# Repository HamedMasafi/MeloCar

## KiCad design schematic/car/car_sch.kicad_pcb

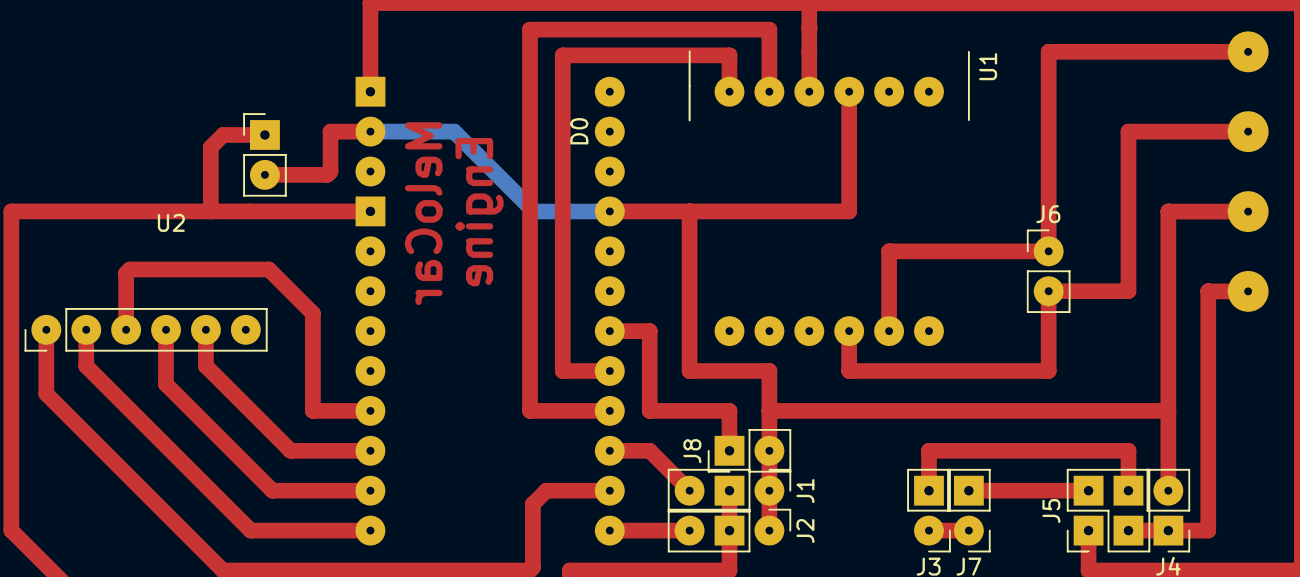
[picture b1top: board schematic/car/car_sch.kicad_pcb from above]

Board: 2 copper layers, 11 parts (1 on the bottom side), 17 nets.

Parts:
A3: Arduino_Pro_Mini_Socket_NoSPH
J1: Led; PinHeader_1x03_P2.54mm_Vertical
J2: Servo; PinHeader_1x03_P2.54mm_Vertical
J3: Battery; PinHeader_1x02_P2.54mm_Vertical
J4: Power; PinHeader_1x02_P2.54mm_Vertical
J5: Switch; PinHeader_2x02_P2.54mm_Vertical
J6: MOTOR-CTRL; PinHeader_1x02_P2.54mm_Vertical
J7: BarGraph; PinHeader_1x02_P2.54mm_Vertical
J8: Horn; PinHeader_1x02_P2.54mm_Vertical
U1: DRV8833PW; TSSOP-16_4.4x5mm_P0.65mm
U2: NRF24L01_Breakout; NRF24L01

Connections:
+5V: A3.Vcc1 (Vcc), J1.2, J2.2, U2.2 (VCC)
+8V: A3.RAW, J4.1, J5.1, J5.3, U1.11 (VCP)
+BATT: J3.2, J5.2, J5.4, J7.2
-BATT: J3.1, J7.1
GND: A3.GND1 (GND), A3.GND2 (GND), J1.1, J2.1, J4.2, J8.2, U1.13 (GND), U2.1 (GND)
NRF_CE: A3.D8, U2.3 (CE)
NRF_CSN: A3.D10 (D10_CS), U2.4 (~CSN)
NRF_MISO: A3.D12 (D12_MISO), U2.7 (MISO)
NRF_MOSI: A3.D11 (D11_MOSI), U2.6 (MOSI)
NRF_SCK: A3.D13 (D13_SCK), U2.5 (SCK)
unnamed: J6.1, U1.2 (AOUT1)
unnamed: J6.2, U1.4 (AOUT2)
PIN_HORN: A3.D4, J8.1
PIN_LED: A3.D7, J1.3
PIN_MOTOR_1: A3.D5, U1.16 (AIN1)
PIN_MOTOR_2: A3.D6, U1.15 (AIN2)
PIN_SERVO: A3.D9, J2.3

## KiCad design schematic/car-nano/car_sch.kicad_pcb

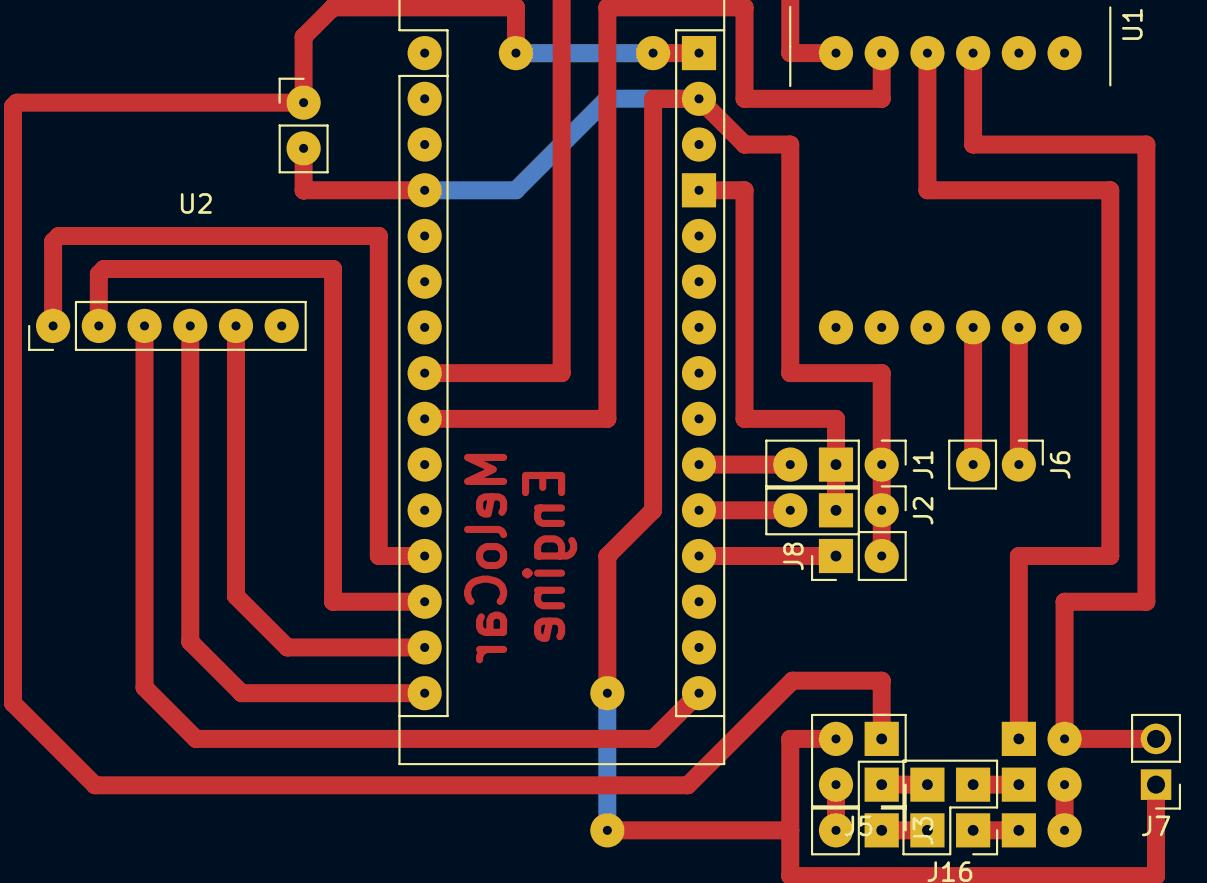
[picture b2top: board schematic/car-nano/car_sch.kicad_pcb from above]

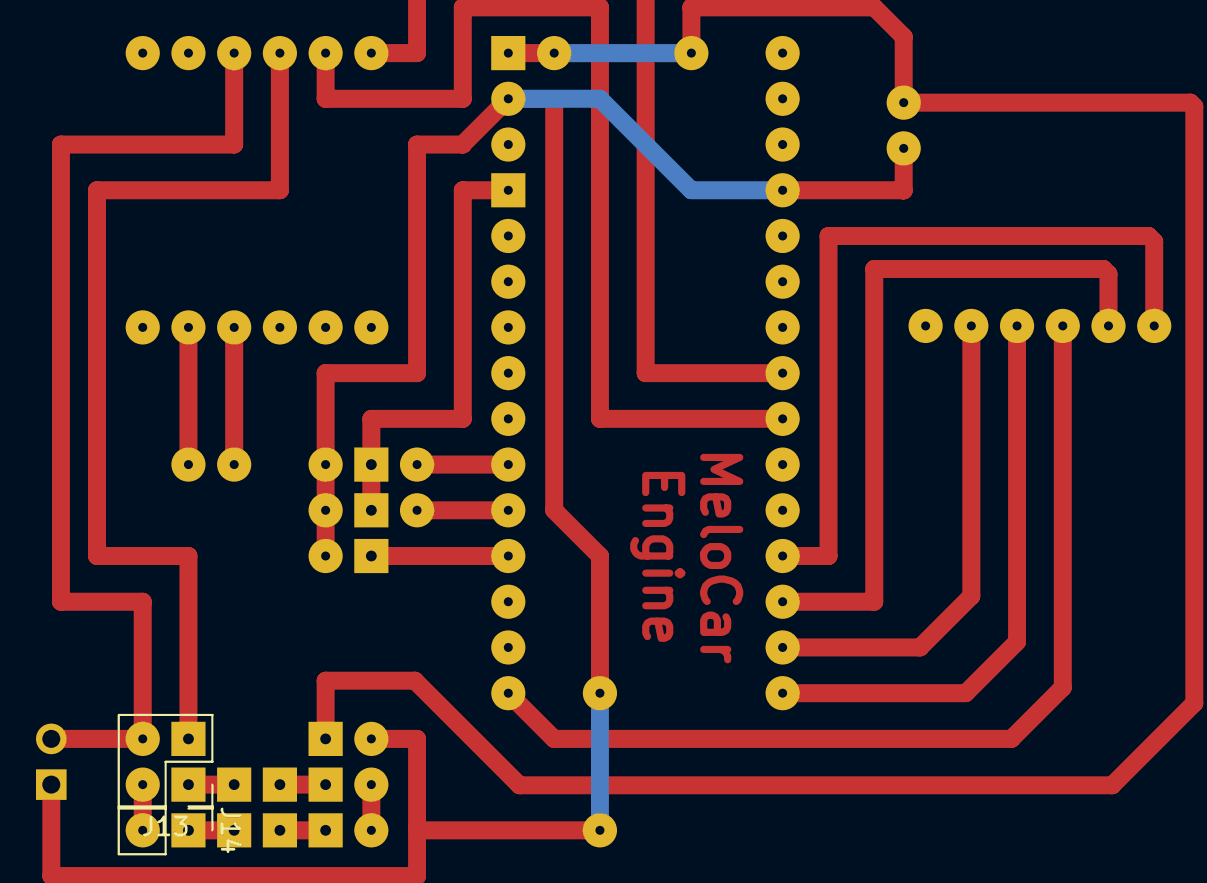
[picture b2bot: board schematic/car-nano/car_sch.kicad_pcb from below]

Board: 2 copper layers, 13 parts (2 on the bottom side), 22 nets.

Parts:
A2: Arduino_Nano_Every; Arduino_Nano
J1: Led; PinHeader_1x03_P2.54mm_Vertical
J2: Servo; PinHeader_1x03_P2.54mm_Vertical
J3: Input-Micro; PinHeader_1x02_P2.54mm_Vertical
J5: Regulator-5v; PinHeader_2x02_P2.54mm_Vertical
J6: MOTOR-CTRL; PinHeader_1x02_P2.54mm_Vertical
J7: Motor_Power; PinHeader_1x02_P2.54mm_Vertical
J8: Horn; PinHeader_1x02_P2.54mm_Vertical
J13: Regulator-9v; PinHeader_2x02_P2.54mm_Vertical
J14: Input-Motor; PinHeader_1x02_P2.54mm_Vertical
J16: Button; PinHeader_2x02_P2.54mm_Vertical
U1: DRV8833PW; TSSOP-16_4.4x5mm_P0.65mm
U2: NRF24L01_Breakout; NRF24L01

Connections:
+5V: A2.30 (VIN), J1.2, J2.2, J5.3, U2.2 (VCC)
+9V: J13.3, U1.11 (VCP)
GND1: J7.2, J13.4, U1.13 (GND)
GND2: A2.4 (GND), A2.29 (GND), J1.1, J2.1, J5.4, J7.1, J8.2, U2.1 (GND)
NRF_CE: A2.12 (D9), U2.3 (CE)
NRF_CSN: A2.13 (D10), U2.4 (~CSN)
NRF_MISO: A2.14 (MOSI), U2.7 (MISO)
NRF_MOSI: A2.15 (MISO), U2.6 (MOSI)
NRF_SCK: A2.16 (SCK), U2.5 (SCK)
unnamed: J3.2, J5.2
unnamed: J6.1, U1.2 (AOUT1)
unnamed: J6.2, U1.4 (AOUT2)
unnamed: J13.1, J16.3
unnamed: J13.2, J14.2
unnamed: J14.1, J16.1
unnamed: J3.1, J16.2
unnamed: J5.1, J16.4
PIN_HORN: A2.19 (A0), J8.1
PIN_LED: A2.21 (A2), J1.3
PIN_MOTOR_1: A2.8 (D5), U1.16 (AIN1)
PIN_MOTOR_2: A2.9 (D6), U1.15 (AIN2)
PIN_SERVO: A2.20 (A1), J2.3

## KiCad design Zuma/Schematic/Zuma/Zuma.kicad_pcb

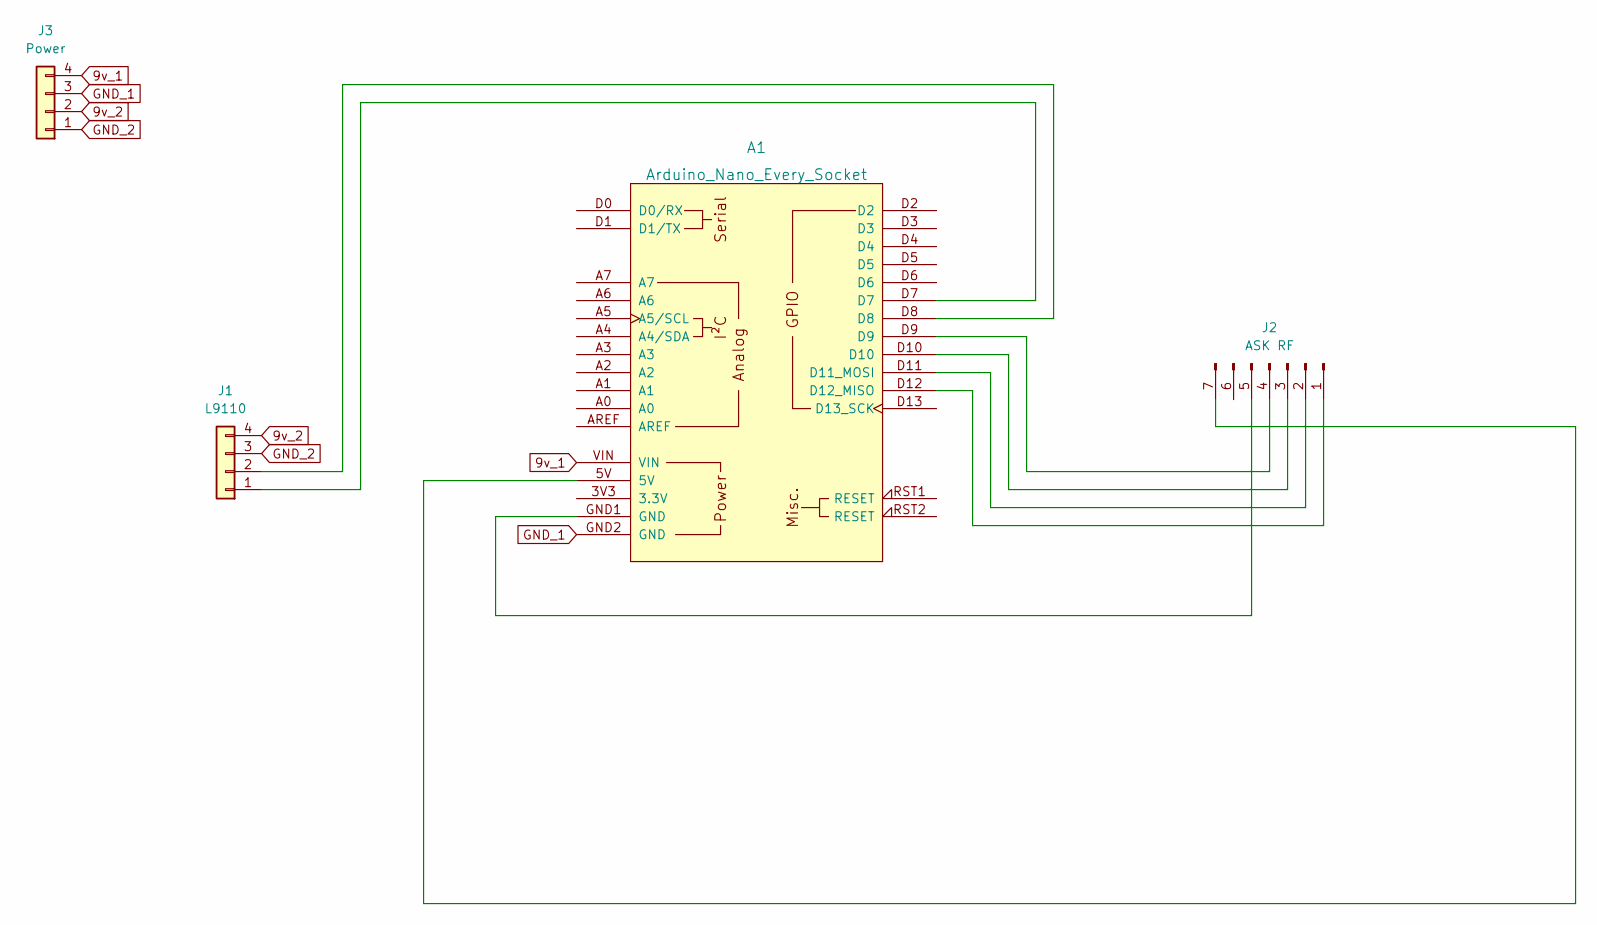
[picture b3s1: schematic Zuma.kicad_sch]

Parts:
A1: Arduino_Nano_Every_Socket
J1: L9110; PinHeader_1x04_P2.54mm_Vertical
J2: ASK RF; PinHeader_1x07_P2.54mm_Vertical
J3: Power; PinHeader_1x04_P2.54mm_Vertical

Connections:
9v_1: A1.VIN, J3.4
9v_2: J1.4, J3.2
GND_1: A1.GND2 (GND), J3.3
GND_2: J1.3, J3.1
unnamed: A1.D7, J1.1
unnamed: A1.D8, J1.2
unnamed: A1.D10, J2.3
unnamed: A1.D11 (D11_MOSI), J2.2
unnamed: A1.D12 (D12_MISO), J2.1
unnamed: A1.GND1 (GND), J2.5
unnamed: A1.D9, J2.4
unnamed: A1.5V, J2.7

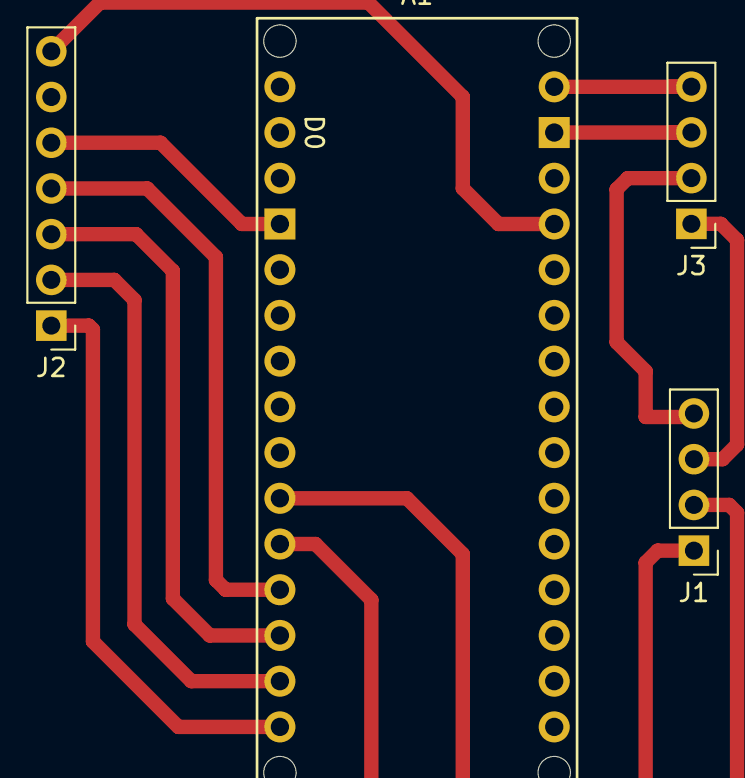
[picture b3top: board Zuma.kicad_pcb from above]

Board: 2 copper layers, 4 parts (0 on the bottom side), 12 nets.

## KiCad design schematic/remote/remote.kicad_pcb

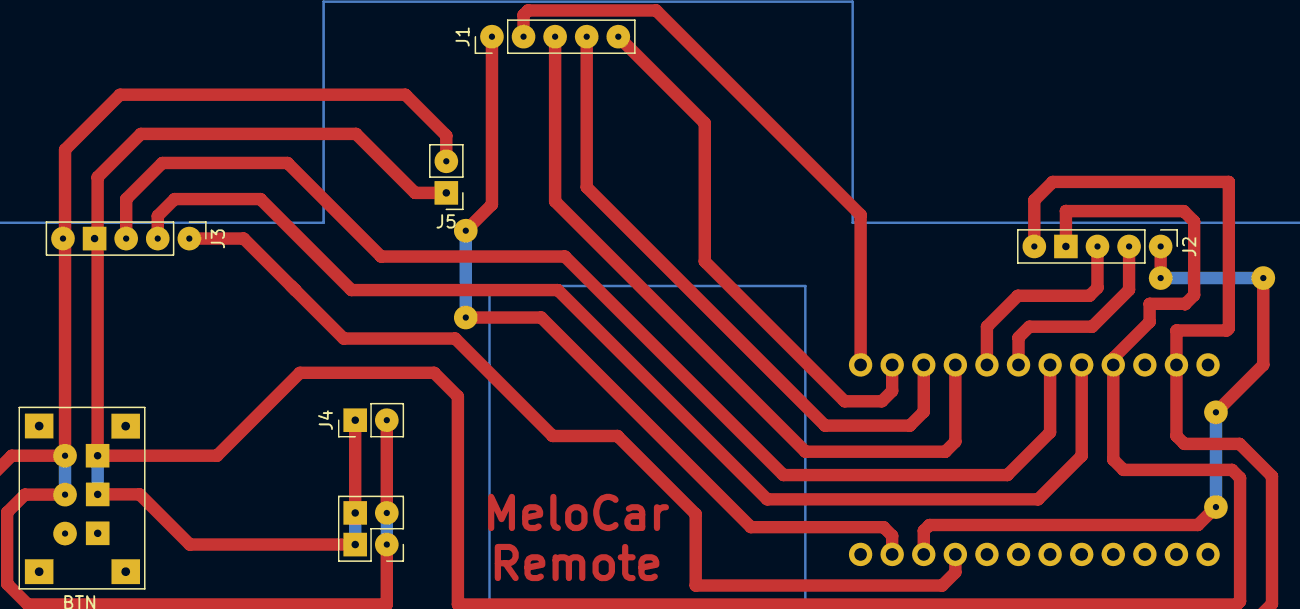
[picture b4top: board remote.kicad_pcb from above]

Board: 2 copper layers, 7 parts (1 on the bottom side), 13 nets.

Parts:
BTN: PushButton_6_pin
J1: Conn_01x05_Male; PinHeader_1x05_P2.54mm_Vertical
J2: Joystick_Left; PinHeader_1x05_P2.54mm_Vertical
J3: Joystick_Right; PinHeader_1x05_P2.54mm_Vertical
J4: Micro-Power-IN; PinHeader_1x02_P2.54mm_Vertical
J5: NRF-Power; PinHeader_1x02_P2.54mm_Vertical
U1: ARDUINO_PRO_MINI; MODULE_ARDUINO_PRO_MINI

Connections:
+5V: BTN.3, BTN.5, J2.4, J3.4, J4.1, J5.1, U1.JP6_4 (VCC_1)
GND: BTN.4, BTN.6, J2.5, J3.5, J4.2, J5.2, U1.JP6_2 (GND_1)
unnamed: J1.1, U1.JP7_2 (D8)
unnamed: J1.2, U1.JP6_12 (D10)
unnamed: J1.3, U1.JP6_9 (SCK)
unnamed: J1.4, U1.JP6_10 (MISO)
unnamed: J1.5, U1.JP6_11 (MOSI)
unnamed: J2.1, U1.JP7_3 (D7)
unnamed: J2.3, U1.JP6_8 (A0)
unnamed: J3.1, U1.JP7_4 (D6)
unnamed: J3.2, U1.JP6_5 (A3)
unnamed: J3.3, U1.JP6_6 (A2)
unnamed: J2.2, U1.JP6_7 (A1)

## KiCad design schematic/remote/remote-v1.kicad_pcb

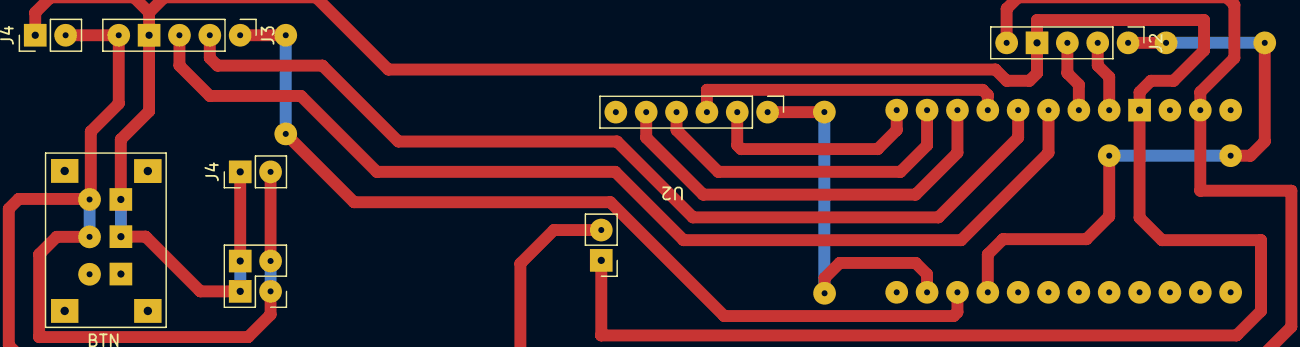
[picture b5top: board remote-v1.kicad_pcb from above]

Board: 2 copper layers, 7 parts (1 on the bottom side), 13 nets.

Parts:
BTN: PushButton; PushButton_6_pin
J2: Joystick_Right; PinHeader_1x05_P2.54mm_Vertical
J3: Joystick_Left; PinHeader_1x05_P2.54mm_Vertical
J4, J4#2: Power-IN; PinHeader_1x02_P2.54mm_Vertical
U1: ARDUINO_PRO_MINI; MODULE_ARDUINO_PRO_MINI
U2: NRF24L01

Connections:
+5V: BTN.3, BTN.5, J2.4, J3.4, J4.1, J4#2.1, U1.JP6_4 (VCC_1), U2.2 (VCC)
GND: BTN.4, BTN.6, J2.5, J3.5, J4.2, J4#2.2, U1.JP6_2 (GND_1), U2.1 (GND)
unnamed: J2.1, U1.JP7_4 (D6)
unnamed: J2.2, U1.JP6_5 (A3)
unnamed: J2.3, U1.JP6_6 (A2)
unnamed: J3.1, U1.JP7_3 (D7)
unnamed: J3.2, U1.JP6_8 (A0)
unnamed: J3.3, U1.JP6_7 (A1)
unnamed: U1.JP6_9 (SCK), U2.5 (SCK)
unnamed: U1.JP6_10 (MISO), U2.7 (MISO)
unnamed: U1.JP6_11 (MOSI), U2.6 (MOSI)
unnamed: U1.JP6_12 (D10), U2.4 (~CSN)
unnamed: U1.JP7_2 (D8), U2.3 (CE)

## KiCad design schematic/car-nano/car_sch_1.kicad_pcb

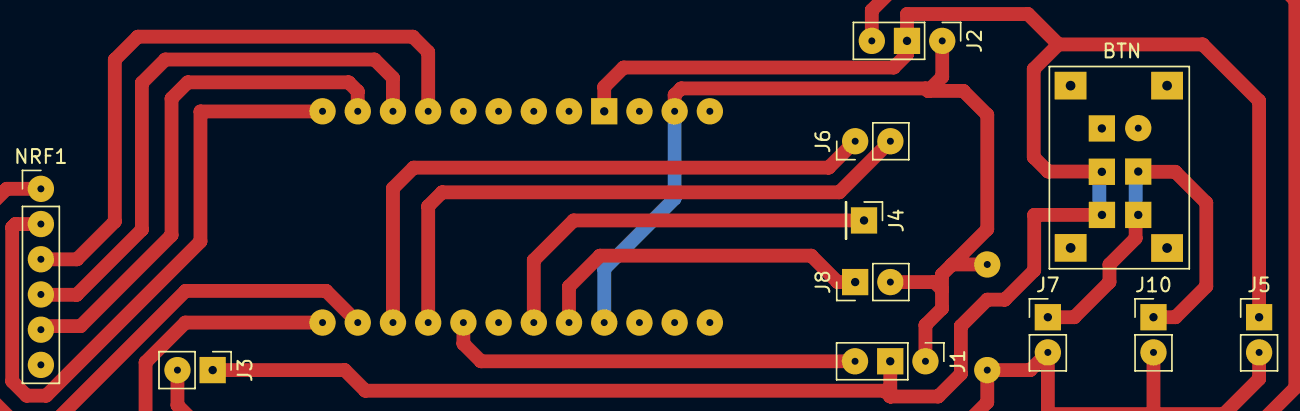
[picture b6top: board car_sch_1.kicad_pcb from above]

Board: 2 copper layers, 12 parts (1 on the bottom side), 14 nets.

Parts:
BTN: PushButton_6_pin
J1: Led; PinHeader_1x03_P2.54mm_Vertical
J2: Servo; PinHeader_1x03_P2.54mm_Vertical
J3: NRF-Power; PinHeader_1x02_P2.54mm_Vertical
J4: Accel; PinHeader_1x01_P2.54mm_Vertical
J5: Micro-Power-IN; PinHeader_1x02_P2.54mm_Vertical
J6: MOTOR-CTRL; PinHeader_1x02_P2.54mm_Vertical
J7: MOTOR-PWR-OUT; PinHeader_1x02_P2.54mm_Vertical
J8: Horn; PinHeader_1x02_P2.54mm_Vertical
J10: Motor-PWR-IN; PinHeader_1x02_P2.54mm_Vertical
NRF1: Conn_01x06_Male; PinHeader_1x06_P2.54mm_Vertical
U1: ARDUINO_PRO_MINI; MODULE_ARDUINO_PRO_MINI

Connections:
+5V: BTN.3, BTN.5, J1.2, J2.2, J3.1, J5.1, U1.JP6_4 (VCC_1)
+12V: BTN.4, BTN.6, J7.1, J10.1
GND: J1.1, J2.1, J3.2, J5.2, J7.2, J8.2, J10.2, U1.JP6_2 (GND_1), U1.JP7_9 (GND_2)
unnamed: J1.3, U1.JP7_5 (D5)
unnamed: J2.3, U1.JP7_1 (D9)
unnamed: J6.1, U1.JP7_3 (D7)
unnamed: J6.2, U1.JP7_4 (D6)
unnamed: J8.1, U1.JP7_8 (D2)
unnamed: NRF1.3, U1.JP6_9 (SCK)
unnamed: NRF1.4, U1.JP6_10 (MISO)
unnamed: NRF1.5, U1.JP6_11 (MOSI)
unnamed: NRF1.2, U1.JP6_12 (D10)
unnamed: NRF1.1, U1.JP7_2 (D8)
unnamed: J4.1, U1.JP7_7 (D3)

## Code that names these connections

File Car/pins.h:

#pragma once

// #define PIN_ACCEL   3
#define PIN_BEEP    4
#define PIN_MOTOR_1 5
#define PIN_MOTOR_2 6
#define LED_PIN     7
#define PIN_SERVO   9

#define PIN_CE      8
#define PIN_CSN     10

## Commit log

2022-10-31 Initial
2022-11-02 wip: nrf
2022-11-05 OOps; ws works
2022-11-07 platformio
2022-11-07 Back to arduino ide
2022-11-07 /stepper/blinker/
2022-11-09 Servo port changed to 5
2022-11-09 Remote
2022-11-17 --wip-- [skip ci]
2022-11-17 wip radio:
2022-11-19 wip: kicad
2022-11-19 larger via
2022-11-20 Remove p folder
2022-11-20 before merge
2022-11-21 Add JoystickReader.h here
2022-12-12 Works
2022-12-12 Ignore backups
2022-12-18 Semo works
2022-12-20 remote workds
2023-01-07 remote changed to v2
2023-01-22 befor merge
2023-02-13 Accel step
2023-02-14 Accel
2023-02-14 Update schematic
2023-02-14 Format code
2023-02-14 New button board
2023-02-15 merge
2023-02-22 Working on it
2023-04-06 schematics
2023-12-04 StressWire
2023-12-06 Better game play
2023-12-06 Fix melody pin
2023-12-06 red led as fault
2023-12-13 Zuma added
2023-12-19 works!!!
2023-12-25 drv8833
2024-01-20 schematic
2024-02-24 Go home
2024-03-02 Works in first test
2024-04-29 Add police light
2024-10-07 Update StressWire
2024-11-15 tempo
2024-11-17 gardener
